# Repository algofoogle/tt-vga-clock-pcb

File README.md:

Matt Venn's ASIC VGA Clock
==========================

* World's first [certified open source hardware](https://certification.oshwa.org/es000023.html) down to the GDS?
* The original design was using an ASIC that was part of the Google sponsored MPW1. Due to [many issues with this first chip](https://www.zerotoasiccourse.com/post/mpw1_silicon/), the current version uses one from the [TinyTapeout 3p5](https://github.com/TinyTapeout/tinytapeout-03p5) experimental test.
* For more details about the design, see [VGA ASIC Clock](https://www.zerotoasiccourse.com/post/vga_clock/). 

# PCB

This PCB started by forking the https://github.com/TinyTapeout/caravel-mvp-pcb template repository. That provides all the minimal necessary components for the chip to work. 
This repo then adds the needed buttons and VGA connector for the clock design.

* [PDF Schematic](doc/schematic.pdf)

# Setup

## Firmware

This needs to be made public and the fw fixed to always select clock.

https://github.com/TinyTapeout/tt3p5-demo-fw/

## PLL config

Needs 31.5MHz for VGA signal. As precise as possible for good timekeeping.
A 9MHz oscillator should also work if using the chip's built in PLL.

Using https://github.com/kbeckmann/caravel-pll-calculator

    matt-desktop:2003 [main]: ./caravel_pll.py generate --clkout 31.5 --clkin 9
    PLL Parameters:

    clkin:    9.00 MHz
    clkout:   31.50 MHz
    clkout90: 31.50 MHz

    PLL Feedback Divider: 14
    PLL Output Divider 1: 4
    PLL Output Divider 2: 4

    Register 0x11: 0x24
    Register 0x12: 0x0e

## Pinning

The chip's pinout is here: https://github.com/TinyTapeout/tinytapeout-03p5/blob/main/verilog/rtl/user_defines.v

The definition of the clock design pins are here: https://github.com/TinyTapeout/tt03p5-vga-clock/blob/main/src/tt_vga_clock.v

### inputs

* 06 clock 
* 07 rst_n
* 08 hours
* 09 mins
* 10 sec

### outputs

* 16 hsync
* 17 vsync
* 18:23 rrggbb

# BOM

TBD

# Errata

# Resources

* Caravel datasheet: https://caravel-harness.readthedocs.io/en/latest
* Version 1 repository is here: https://github.com/mattvenn/vga_clock_pcb

# License

* The ASIC and PCB are licensed under the [Apache2 License](LICENSE)

# Open Source Hardware

This board is an OSHWA approved design: [ES000023](https://certification.oshwa.org/es000023.html)

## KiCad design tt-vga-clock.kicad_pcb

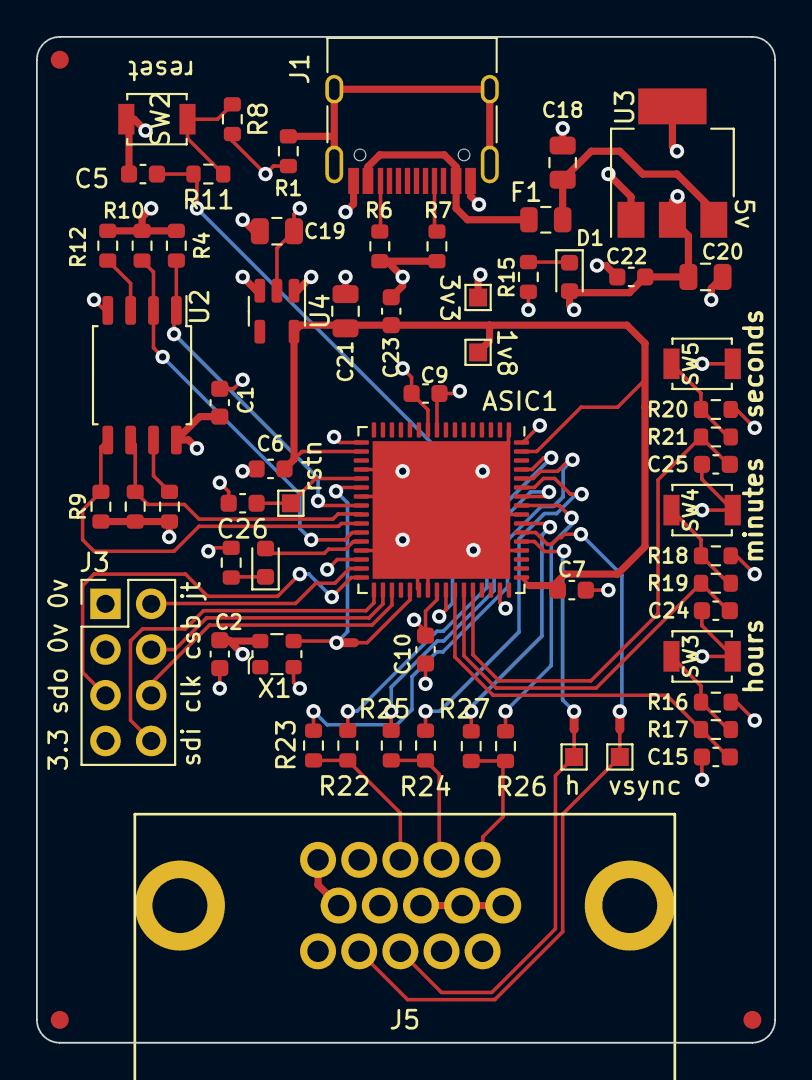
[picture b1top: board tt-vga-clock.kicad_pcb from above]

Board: 4 copper layers, 41.0 x 55.9 mm, 68 parts (0 on the bottom side), 46 nets.

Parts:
C1, C2, C6, C7, C9, C10, C22, C23: 100nF; C_0603_1608Metric
C5, C15, C24, C25, C26: 1uF; C_0603_1608Metric
C18, C19, C21: 10uF; C_0805_2012Metric
C20: 22uF; C_0805_2012Metric
D1, D2: LED; LED_0603_1608Metric
F1: 350mA; Fuse_0805_2012Metric
FID1, FID2, FID3: Fiducial; Fiducial_1mm_Mask2mm
J1: USB_C_Receptacle_USB2.0; USB_C_Receptacle_HRO_TYPE-C-31-M-12
J3: Conn_02x04_Odd_Even; PinHeader_2x04_P2.54mm_Vertical
J5: DE15_Receptacle_HighDensity_MountingHoles; db15
NT1, NT2, NT3: NetTie_2; NetTie-2_SMD_Pad0.5mm
R1: 1M; R_0603_1608Metric
R4, R5, R8, R9, R10, R12, R13, R16, R18, R20: 10k; R_0603_1608Metric
R6, R7, R11, R17, R19, R21: 5.1k; R_0603_1608Metric
R14, R15: 510; R_0603_1608Metric
R22, R24, R26: 500R; R_0603_1608Metric
R23, R25, R27: 1k; R_0603_1608Metric
SW2, SW3, SW4, SW5: B3U-1000P; SW_SPST_B3U-1000P
TP1, TP2, TP3, TP4, TP5: TestPoint; TestPoint_Pad_1.0x1.0mm
U1: Caravel_QFN; QFN-64-1EP_9x9mm_P0.5mm_EP7.65x7.65mm
U2: W25Q32JVSS; SOIC-8_5.23x5.23mm_P1.27mm
U3: AZ1117-3.3; SOT-223-3_TabPin2
U4: AP2112K-1.8; SOT-23-5
X1: 31.5MHz; Oscillator_SMD_ECS_2520MV-xxx-xx-4Pin_2.5x2.0mm

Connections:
+1V8: C6.1, C7.2, C21.1, C23.1, TP5.1, U1.18 (vccd), U1.49 (vccd1), U1.63 (vccd2), U4.5 (VOUT)
+3V3: C1.1, C2.2, C5.1, C9.2, C10.1, C15.1, C19.1, C20.1, C22.1, C24.1, C25.1, D1.2 (A), J3.7, R4.1, R5.1, R9.1, R10.1, R12.2, R13.2, SW2.2, SW3.2, SW4.2, SW5.2, TP4.1, U1.9 (vdda2), U1.17 (vddio), U1.30 (vdda), U1.40 (vdda1), U1.47 (vdda1), U1.64 (vddio), U2.8 (VCC), U3.2 (VO), U4.1 (VIN), U4.3 (EN), X1.4 (VDD)
+5V: C18.1, F1.2, U3.3 (VI)
/blue: J5.3, R22.2, R23.2
/green: J5.2, R24.2, R25.2
/hsync: J5.13, NT1.2, TP1.1
/prj_io7: C5.2, R11.2, U1.41 (mprj_io[7])
/prj_io8: C15.2, R17.2, U1.42 (mprj_io[8])
/prj_io9: C24.2, R19.2, U1.43 (mprj_io[9])
/prj_io10: C25.2, R21.2, U1.44 (mprj_io[10])
/prj_io16: NT1.1, U1.53 (mprj_io[16])
/prj_io17: NT2.1, U1.54 (mprj_io[17])
/prj_io18: R27.1, U1.55 (mprj_io[18])
/prj_io19: R26.1, U1.57 (mprj_io[19])
/prj_io20: R25.1, U1.58 (mprj_io[20])
/prj_io21: R24.1, U1.59 (mprj_io[21])
/prj_io22: R23.1, U1.60 (mprj_io[22])
/prj_io23: R22.1, U1.61 (mprj_io[23])
/red: J5.1, R26.2, R27.2
/vsync: J5.14, NT2.2, TP2.1
GND: C1.2, C2.1, C6.2, C7.1, C9.1, C10.2, C18.2, C19.2, C20.2, C21.2, C22.2, C23.2, C26.2, J1.A1 (GND), J1.A12 (GND), J1.B1 (GND), J1.B12 (GND), J3.1, J3.3, J5.5, J5.6, J5.7, J5.8, J5.10, R1.2, R6.2, R7.2, R8.2, R14.2, R15.2, R16.2, R18.2, R20.2, U1.1 (vssa2), U1.10 (vssd2), U1.20 (vssa), U1.23 (vssd), U1.29 (vssio), U1.38 (vssa1), U1.39 (vssd1), U1.52 (vssa1), U1.56 (vssio), U1.65 (ThermalPad), U2.4 (GND), U3.1 (GND), U4.2 (GND), X1.2 (GND)
HK_CSB: J3.4, U1.34 (mprj_io[3]_CSB)
HK_JTAG: J3.2, U1.31 (mprj_io[0]_JTAG)
HK_SCK: J3.6, U1.35 (mprj_io[4]_SCK)
HK_SDI: J3.8, U1.33 (mprj_io[2]_SDI)
HK_SDO: J3.5, U1.32 (mprj_io[1]_SDO)
unnamed: D1.1 (K), R15.1
unnamed: D2.1 (K), R14.1
unnamed: J1.A5 (CC1), R7.1
unnamed: J1.B5 (CC2), R6.1
unnamed: J1.S1 (SHIELD), R1.1
unnamed: R8.1, R11.1, SW2.1
unnamed: R16.1, R17.1, SW3.1
unnamed: R18.1, R19.1, SW4.1
unnamed: R20.1, R21.1, SW5.1
unnamed: R12.1, U2.3 (IO2)
unnamed: R13.1, U2.7 (IO3)
VBUS: F1.1, J1.A4 (VBUS), J1.A9 (VBUS), J1.B4 (VBUS), J1.B9 (VBUS)
flash_clk: R5.2, U1.25 (flash_clk), U2.6 (CLK)
flash_csb: R4.2, U1.24 (flash_csb), U2.1 (~CS)
flash_io0: R9.2, U1.26 (flash_io0), U2.5 (DI(IO0))
flash_io1: R10.2, U1.27 (flash_io1), U2.2 (DO(IO1))
gpio: D2.2 (A), U1.28 (gpio)
osc_out: NT3.1, U1.22 (clock), X1.3 (OUT)
ser_tx: NT3.2, U1.37 (mprj_io[6]_ser_tx)
~SOC_RST: C26.1, TP3.1, U1.21 (resetb)

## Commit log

2023-12-27 pinout for buttons, delete unneeded parts
2023-12-27 schematic done
2023-12-28 start layout
2023-12-28 first pass layout
2023-12-28 oshw mark, better silk, edge cuts, all nets connected
2023-12-28 use correct db15 fp
2023-12-30 model for db15
2023-12-30 fix link#
2023-12-30 pinout formatting
2024-02-07 Increase space (ASIC east) for next rev; tidy west/south traces

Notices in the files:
tt-vga-clock.kicad_pcb:
(C) 2023 Pat Deegan
